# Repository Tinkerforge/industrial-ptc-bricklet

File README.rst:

Industrial PTC Bricklet
=======================

This repository contains the firmware source code and the hardware design
files. The documentation generator configs can be found at
https://github.com/Tinkerforge/generators

Repository Content
------------------

software/:
 * examples/: Examples for all supported languages
 * build/: Compiled files
 * src/: Source code of firmware
 * Makefile: Makefile to build project

hardware/:
 * Contains KiCad project files and additionally schematics as PDF

datasheets/:
 * Contains datasheets for sensors and complex ICs that are used

Hardware
--------

The hardware is designed with the open source EDA Suite KiCad
(http://www.kicad.org). Before you are able to open the files,
you have to install the Tinkerforge kicad-libraries
(https://github.com/Tinkerforge/kicad-libraries). You can either clone
them directly in hardware/ or clone them in a separate folder and
symlink them into hardware/
(ln -s kicad_path/kicad-libraries project_path/hardware). After that you
can open the .pro file in hardware/ with KiCad and from there view and
modify the schematics and the PCB layout.

Software
--------

If you want to do your own Brick/Bricklet firmware development we highly
recommend that you use our build environment setup script and read the
tutorial (https://www.tinkerforge.com/en/doc/Tutorials/Tutorial_Build_Environment/Tutorial.html).

To compile the C code we recommend you to install the newest GNU Arm Embedded
Toolchain (https://launchpad.net/gcc-arm-embedded/+download).
You also need to install bricklib2 (https://github.com/Tinkerforge/bricklib2).

You can either clone it directly in software/src/ or clone it in a
separate folder and symlink it into software/src/
(ln -s bricklib_path/bricklib2 project_path/software/src/). Finally make sure to
have CMake installed (http://www.cmake.org/cmake/resources/software.html).

After that you can build the firmware by invoking make in software/.
The firmware (.zbin) can then be found in software/build/ and uploaded
with brickv (click button "Flashing" on start screen).

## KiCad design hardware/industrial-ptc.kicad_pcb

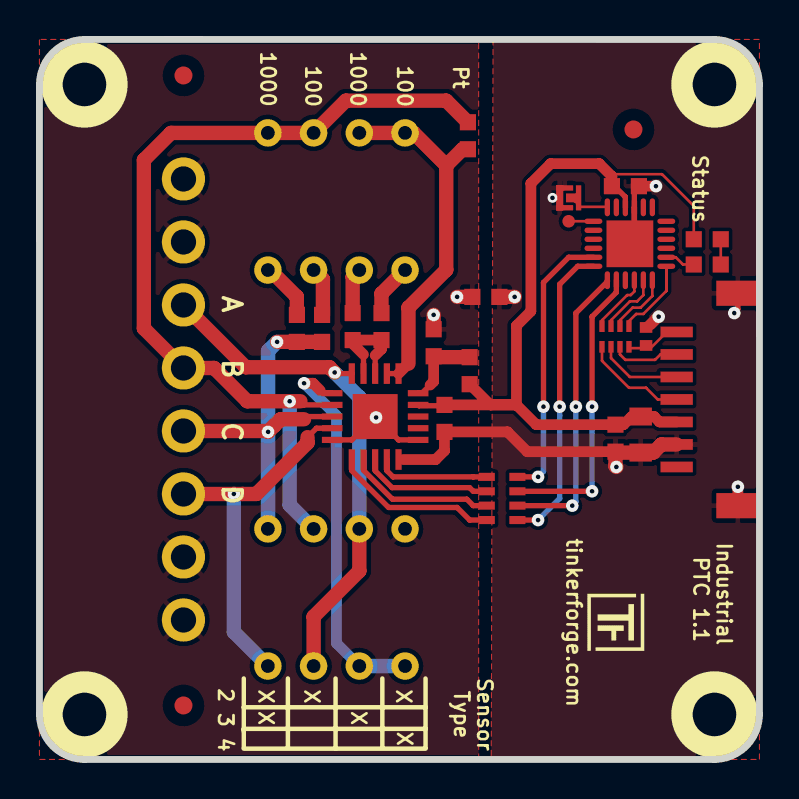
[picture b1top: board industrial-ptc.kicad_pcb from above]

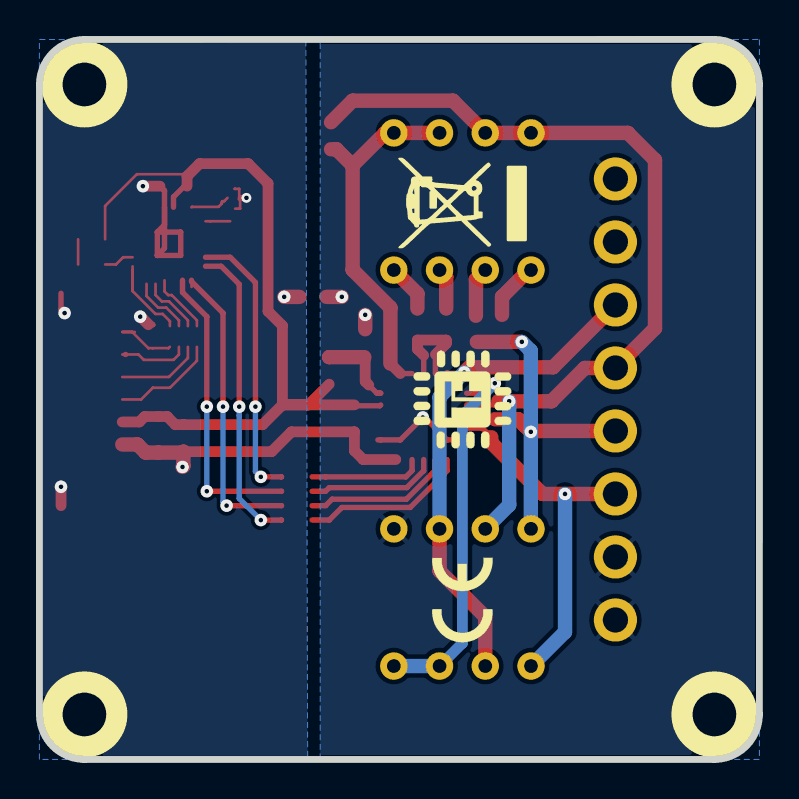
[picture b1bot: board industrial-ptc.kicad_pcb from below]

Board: 2 copper layers, 40.0 x 40.0 mm, 34 parts (2 on the bottom side), 35 nets.

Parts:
C1: 220pF; C0402F
C2: 10uF; C0805
C3, C4, C5, C6, C8: 100nF; C0603F
C7: 10nF; C0603F
D1: blue; D0603F
FB1, FB2: FB; R0603F
Fiducial_Mark: VAL**; Fiducial_Mark
Fiducial_Mark#2, Fiducial_Mark#3: VAL**; Fiducial_Mark
P1: CON-SENSOR; CON-SENSOR2
P2: Debug; DEBUG_PAD
P3: Boot; SolderJumper
P4: CONN_01X08; OQ_8P
R1: 1k; R0603F
R2: 390 0.1%; R0603F
R3: 3k9 0.1%; R0603F
R4: 10M; R0603F
RP1: 82; 4X0402
RP2: 100; 0603X4
SW1, SW2: SW_DIP_4; SW_DIP_4_THT
U1: XMC1100; QFN24-4x4mm-0.5mm
U2: MAX31865; QFN-20-5x5
U3, U4, U5, U6: DRILL; DRILL_NP
VAL: CE_5mm
VAL#2: WEEE_7mm

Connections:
AGND: C6.2, FB1.1, P4.1, P4.2, P4.7, P4.8, SW2.1, U2.10 (AGND2), U2.16 (AGND1), U2.EP (AGND)
FORCE2: SW2.7, SW2.8, U2.6 (FORCE2)
FORCE+: P4.3, SW2.2, SW2.6, U2.5 (FORCE+)
FORCE-: P4.6, SW2.5, U2.9 (FORCE-)
GND: C1.2, C2.2, C3.2, C4.2, C5.1, FB1.2, P1.2, P1.EP, P3.1, U1.9 (VSSP/VSS), U1.EXP (VSSP), U2.15 (DGND)
M-CLK: RP2.6 (R3), U1.19 (P0.8_IO)
M-CS: RP2.7 (R2), U1.20 (P0.9_IO)
M-MISO: RP2.8 (R1), U1.17 (P0.6_IO)
M-MOSI: RP2.5 (R4), U1.18 (P0.7_IO)
unnamed: C1.1, P1.7, RP1.4
unnamed: C6.1, FB2.2, U2.20 (AVDD)
unnamed: C7.2, SW1.6
unnamed: C8.2, SW1.5
unnamed: D1.2 (K), R1.2
unnamed: P1.4, RP1.1
unnamed: P1.5, RP1.2
unnamed: P1.6, RP1.3
unnamed: P2.1, U1.13 (P1.1_IHO)
unnamed: P3.2, U1.12 (P1.2_IHO)
unnamed: R1.1, U1.2 (P2.1_AIO)
unnamed: R2.1, SW1.8
unnamed: R2.2, R3.2, U2.3 (REFIN-), U2.4 (ISENSOR)
unnamed: R3.1, SW1.7
unnamed: R4.1, SW1.1, SW1.2, U2.1 (BIAS), U2.2 (REFIN+)
unnamed: RP2.1, U2.14 (SDO)
unnamed: RP2.2, U2.13 (nCS)
unnamed: RP2.3, U2.12 (SCLK)
unnamed: RP2.4, U2.11 (SDI)
RTDIN+: P4.4, R4.2, SW1.3, SW1.4, SW2.3, U2.7 (RTDIN+)
RTDIN-: C7.1, C8.1, P4.5, SW2.4, U2.8 (RTDIN-)
S-CLK: RP1.7 (R2), U1.23 (P0.14_IO)
S-CS: RP1.8 (R1), U1.22 (P0.13_IO)
S-MISO: RP1.5 (R4), U1.1 (P2.0_AIO)
S-MOSI: RP1.6 (R3), U1.24 (P0.15_IO)
VCC: C2.1, C3.1, C4.1, C5.2, D1.1 (A), FB2.1, P1.3, U1.10 (VDDP/VDD), U2.19 (DVDD)

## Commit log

2020-06-09 Add empty gitignore
2020-06-18 new pcb design
2020-06-18 ready for prototype
2020-09-03 Add Industrial PTC Bricklet firmware
2020-10-16 uc: Fix divisor type.
2020-10-27 Add examples
2021-04-06 add pin1 marking
2021-04-28 add schematic
2021-04-28 add 3d data
2021-05-03 examples: Improve object name
2021-05-27 readme: Remove in-development marker
2021-05-27 Update changelog
2021-09-20 Fix bug in sensor connected callback delivery logic
    and add 500ms debounce to connected value
2021-09-20 Add rev for v2.0.1
2021-10-25 Update KiCad link
    https://www.kicad.org/blog/2021/10/Avoid-links-to-former-kicad-domain/
2022-04-19 examples: uc: Rename TF_HalContext to TF_HAL.
2022-04-20 Improve MAX31865/SPI error handling
2022-04-20 Add ref for 2.0.2
2022-04-27 uc: Adapt to bindings changes
2022-07-06 Add license files.
2022-12-12 Hardware: Updated files to Kicad 6, added 10MOhm resistor for better disconnect detection
2022-12-12 Hardware: changed the silkscreen from to 1.1
2025-01-09 Fix integer overflow in moving average at temperatures above 325°C
2025-01-09 Add ref for 2.0.3

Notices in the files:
hardware/industrial-ptc.kicad_pcb:
Licensed under CERN OHL v.1.1
Copyright (©) 2020, T.Schneidermann
Copyright Tinkerforge GmbH 2020.
This documentation describes Open Hardware and is licensed under the
CERN OHL v. 1.1.
